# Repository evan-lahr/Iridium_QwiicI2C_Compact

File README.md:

Ultra-compact Qwiic (I²C) breakout for the Iridium 9603/9603N satellite modem (e.g., https://www.sparkfun.com/qwiic-iridium-9603n.html
). Built for space-constrained deployments, it integrates I²C control, power regulation, and modem support circuitry in a footprint only slightly larger than the 9603N itself—ideal for embedded field systems.

See the SparkX thread: https://community.sparkfun.com/t/qwiic-iridium-9603n-bom-firmware/67234/8

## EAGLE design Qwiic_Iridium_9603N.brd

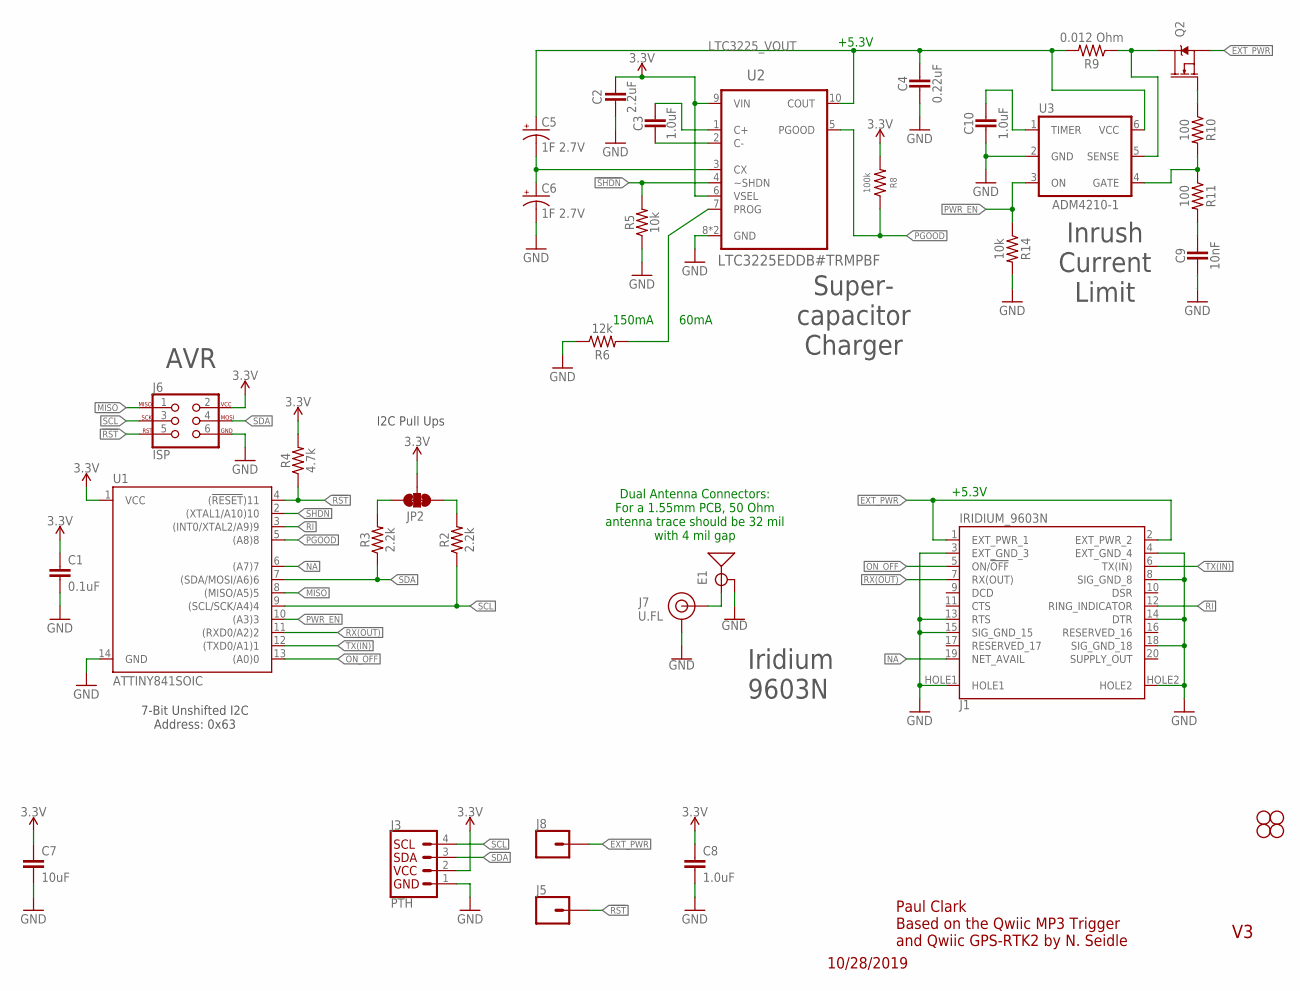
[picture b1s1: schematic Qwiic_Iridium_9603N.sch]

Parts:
C1: 0.1uF; 0603
C2: 2.2uF; 0603
C3, C8, C10: 1.0uF; 0603
C4: 0.22uF; 0603
C5, C6: 1F 2.7V; CPOL-RADIAL-1F-2.7V
C7: 10uF; 0603
C9: 10nF; 0603
E1: ANTENNA-GROUNDEDEDGE_SMA; SMA-EDGE
J1: IRIDIUM_9603N
J3: PTH; 1X04_1MM_RA
J5, J8: CONN_01PTH_NO_SILK_YES_STOP; 1X01_NO_SILK
J6: ISP; 2X3_TEST_POINTS
J7: U.FL
JP2: JUMPER-SMT_3_2-NC_TRACE_SILK; SMT-JUMPER_3_2-NC_TRACE_SILK
JP3, JP4, JP9, JP10: STAND-OFF
Q2: 5.8A/30V/35mΩ; SOT23-3
R2, R3: 2.2k; 0603
R4: 4.7k; 0603
R5, R14: 10k; 0603
R6: 12k; 0603
R8: 100k; 0603
R9: 0.012 Ohm; 0603
R10, R11: 100; 0603
U1: ATTINY841SOIC; ATTINY841
U2: LTC3225EDDB#TRMPBF; DFN300X200-10L
U3: ADM4210-1; TSOT6

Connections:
3.3V: C1.1, C2.1, C7.1, C8.1, J3.2 (VCC), J6.2, JP2.2, R4.2, R8.2, U1.1 (VCC), U2.6 (VSEL), U2.9 (VIN)
!RST: J5.1, J6.5, R4.1, U1.4 ((!RESET!)11)
!SHDN: R5.2, U1.2 ((XTAL1/A10)10), U2.4 (~SHDN)
EXT_PWR: J1.1 (EXT_PWR_1), J1.2 (EXT_PWR_2), J8.1, Q2.2 (S)
GND: C1.2, C2.2, C4.2, C6.-, C7.2, C8.2, C9.2, C10.2, E1.GND@0 (GND), E1.GND@1 (GND), E1.GND@2 (GND), E1.GND@3 (GND), J1.3 (EXT_GND_3), J1.4 (EXT_GND_4), J1.8 (SIG_GND_8), J1.13 (RTS), J1.14 (DTR), J1.15 (SIG_GND_15), J1.18 (SIG_GND_18), J1.HOLE1, J1.HOLE2, J3.1 (GND), J6.6, J7.1 (GND), J7.2 (GND), R5.1, R6.1, R14.2, U1.14 (GND), U2.8 (GND), U2.11 (GND), U3.2 (GND)
LTC3225_VOUT: C4.1, C5.+, R9.2, U2.10 (COUT), U3.6 (VCC)
MISO: J6.1, U1.8 ((MISO/A5)5)
unnamed: C5.-, C6.+, U2.3 (CX)
unnamed: R6.2, U2.7 (PROG)
unnamed: E1.SIG (SIGNAL), J7.FEED (SIGNAL)
unnamed: Q2.3 (D), R9.1, U3.5 (SENSE)
unnamed: C3.2, U2.2 (C-)
unnamed: C3.1, U2.1 (C+)
unnamed: Q2.1 (G), R10.1
unnamed: R10.2, R11.1, U3.4 (GATE)
unnamed: C9.1, R11.2
unnamed: C10.1, U3.1 (TIMER)
NA: J1.19 (NET_AVAIL), U1.6 ((A7)7)
ON_OFF: J1.5 (ON/!OFF!), U1.13 ((A0)0)
PGOOD: R8.1, U1.5 ((A8)8), U2.5 (PGOOD)
PWR_EN: R14.1, U1.10 ((A3)3), U3.3 (ON)
RI: J1.12 (RING_INDICATOR), U1.3 ((INT0/XTAL2/A9)9)
RX(OUT): J1.7 (RX(OUT)), U1.11 ((RXD0/A2)2)
SCL: J3.4 (SCL), J6.3, R2.1, U1.9 ((SCL/SCK/A4)4)
SCL_PU1: JP2.1, R2.2
SDA: J3.3 (SDA), J6.4, R3.1, U1.7 ((SDA/MOSI/A6)6)
SDA_PU1: JP2.3, R3.2
TX(IN): J1.6 (TX(IN)), U1.12 ((TXD0/A1)1)

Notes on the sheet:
Paul Clark Based on the Qwiic MP3 Trigger and Qwiic GPS-RTK2 by N. Seidle
7-Bit Unshifted I2C Address: 0x63
I2C Pull Ups
AVR
+5.3V
150mA
60mA
Super- capacitor Charger
Iridium 9603N
Dual Antenna Connectors: For a 1.55mm PCB, 50 Ohm antenna trace should be 32 mil with 4 mil gap
Inrush Current Limit
10/28/2019

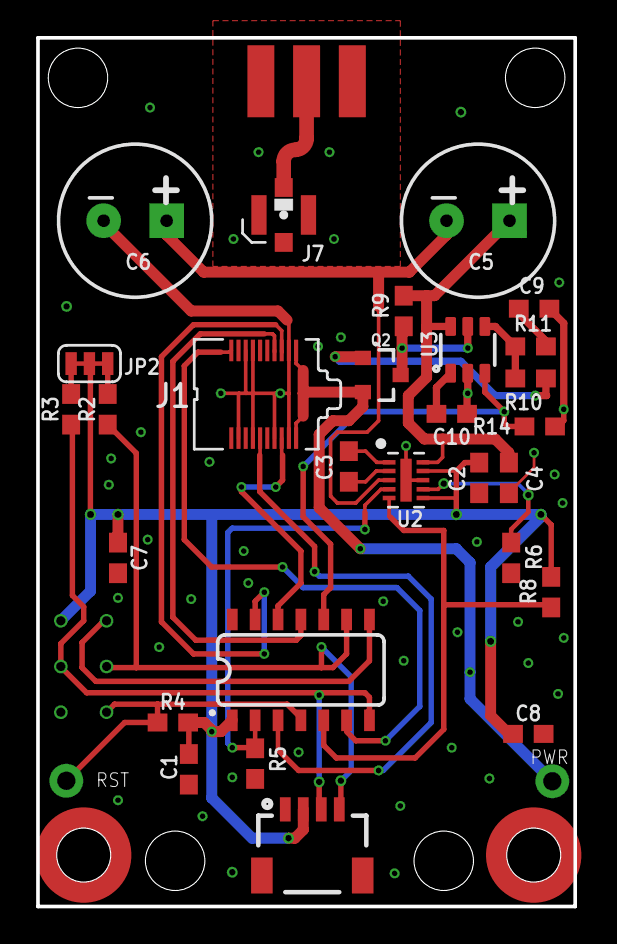
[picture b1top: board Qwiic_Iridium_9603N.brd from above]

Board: 2 copper layers, 29.8 x 48.3 mm, 36 parts (1 on the bottom side), 28 nets.

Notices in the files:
parts and their libraries:
SparkFun-Resistors: Licensing: Creative Commons ShareAlike 4.0 International - https://creativecommons.org/licenses/by-sa/4.0
